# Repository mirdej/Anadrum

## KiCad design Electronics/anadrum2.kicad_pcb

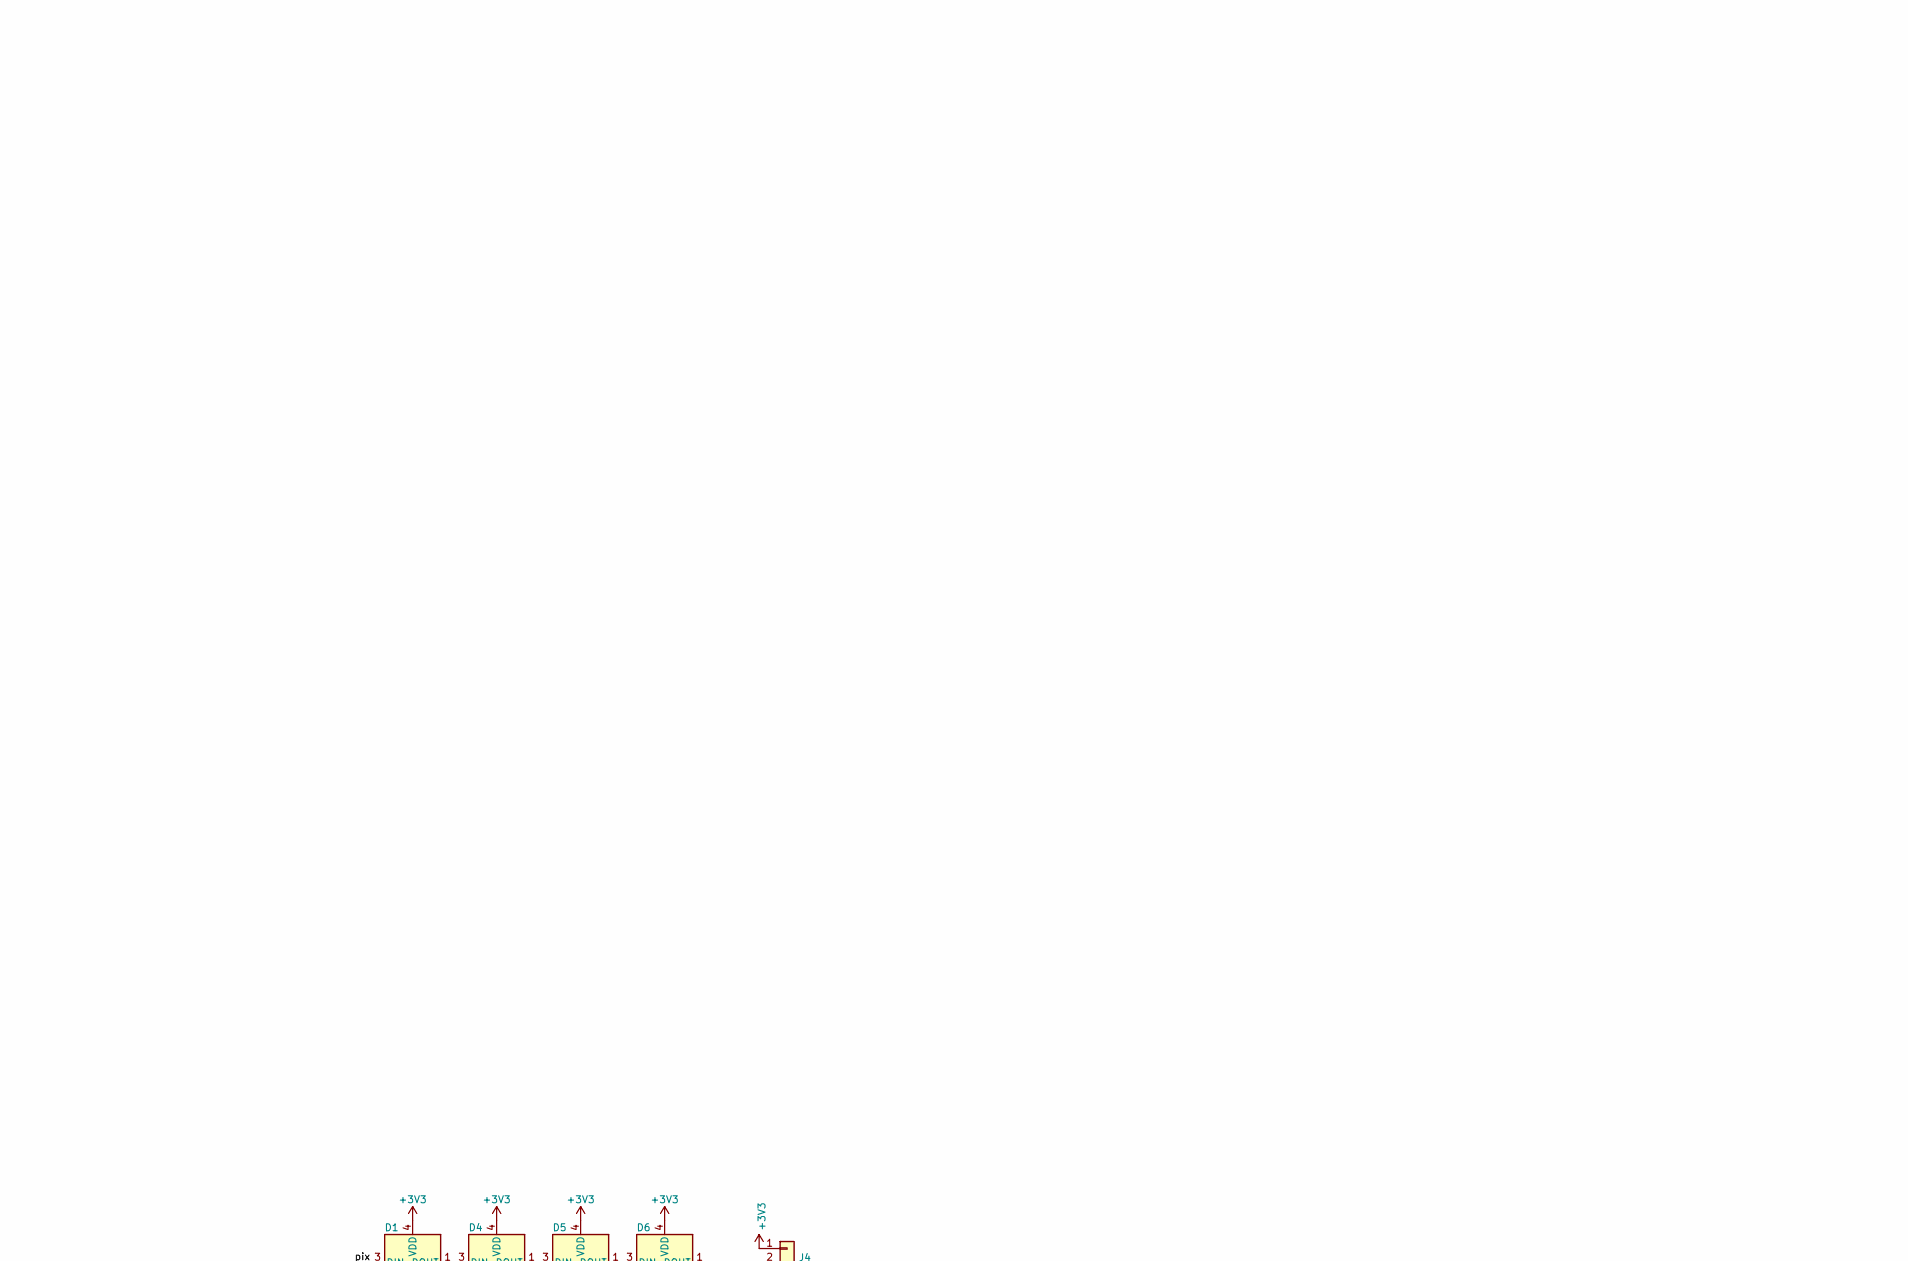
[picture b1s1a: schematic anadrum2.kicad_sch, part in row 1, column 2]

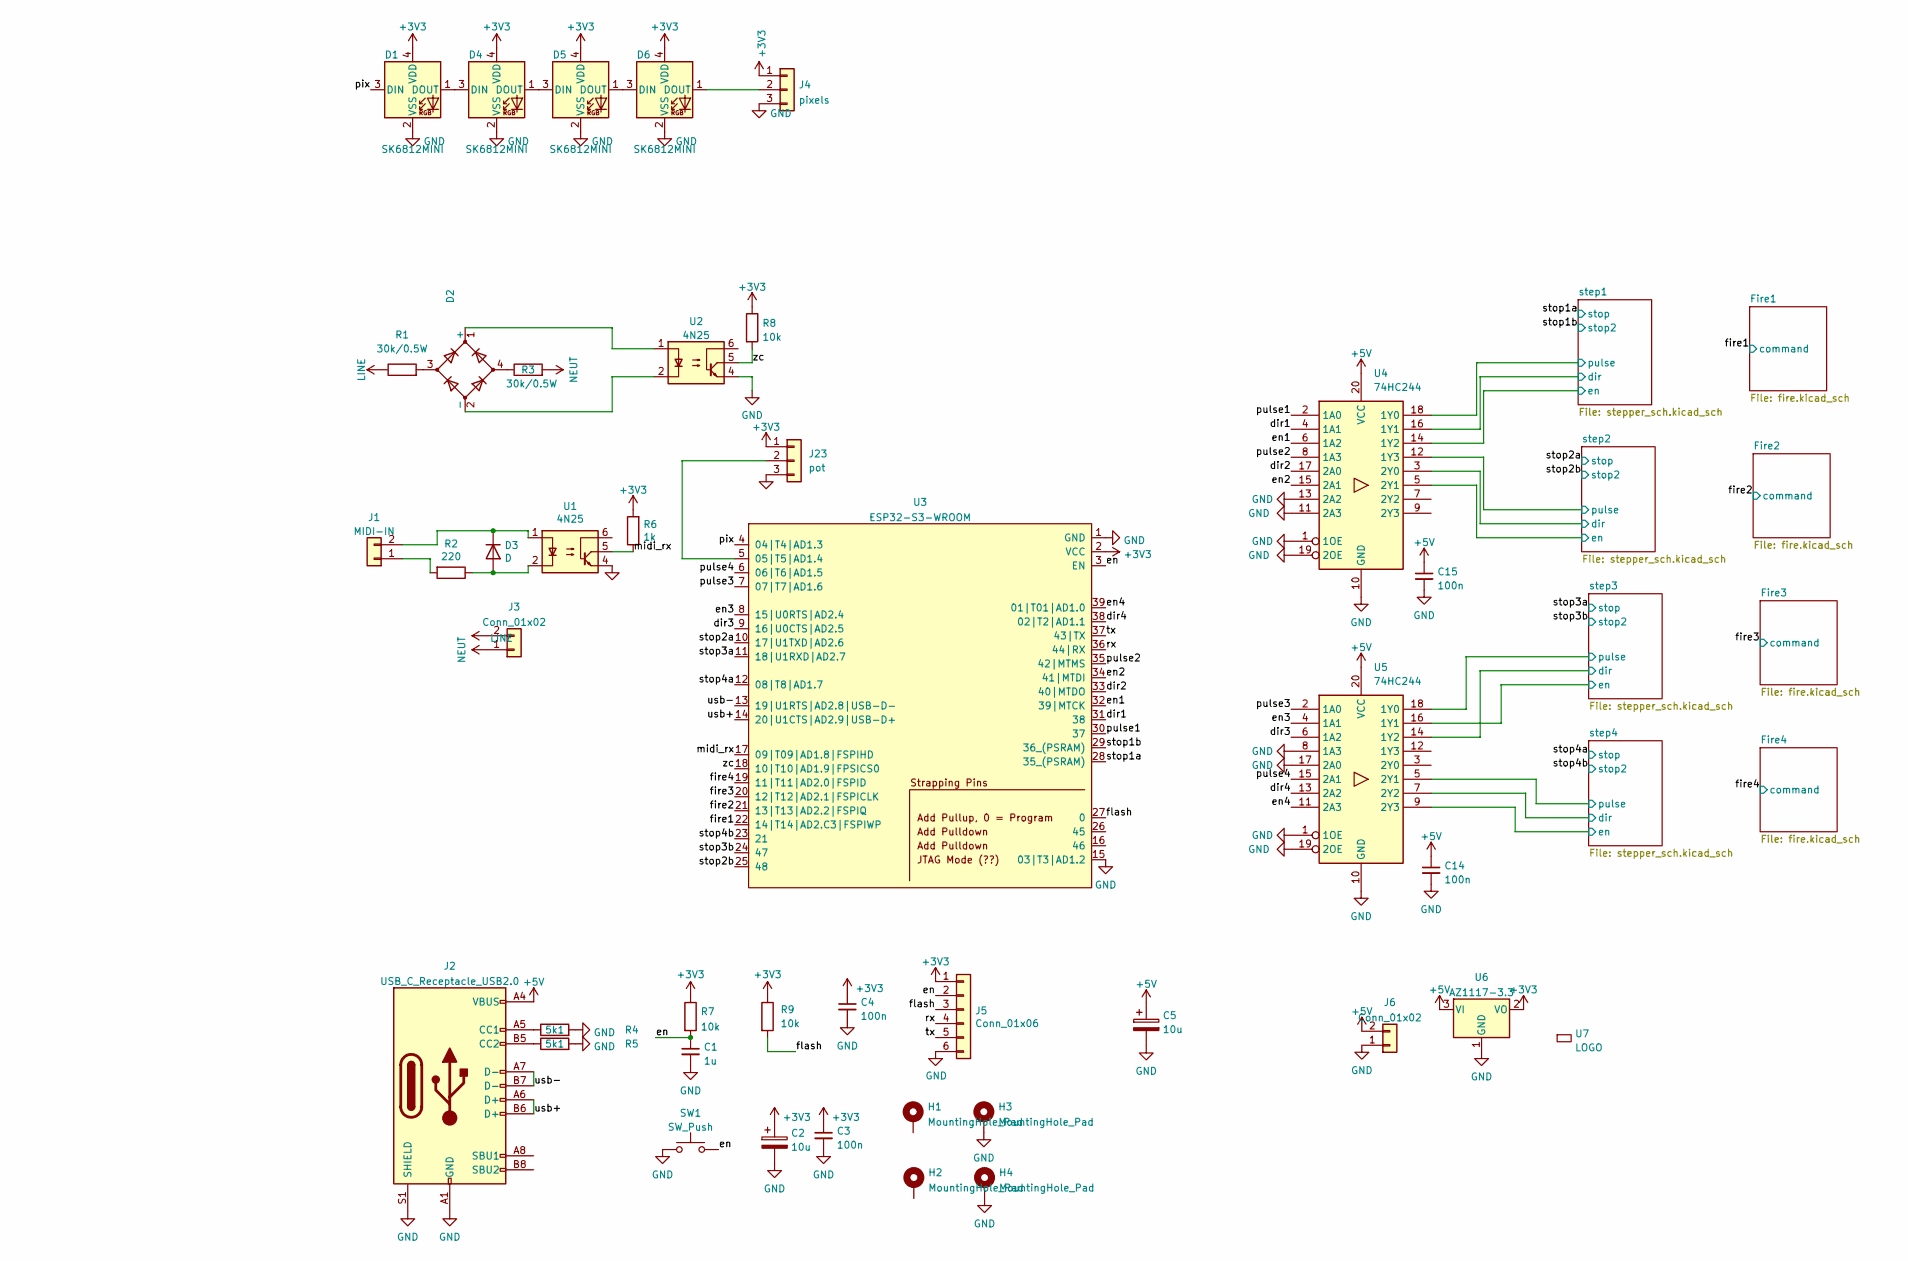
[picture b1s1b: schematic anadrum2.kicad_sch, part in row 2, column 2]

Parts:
C1: 1u; C_0603_1608Metric_Pad1.05x0.95mm_HandSolder
C2, C5: 10u; C_1206_3216Metric_Pad1.42x1.75mm_HandSolder
C3, C4, C14, C15: 100n; C_0603_1608Metric_Pad1.05x0.95mm_HandSolder
D1, D4, D5, D6: SK6812MINI; LED_SK6812MINI_PLCC4_3.5x3.5mm_P1.75mm
D2: D_Bridge_+-AA; Diode_Bridge_Vishay_DFS
D3: D; D_MiniMELF
H1, H2, H3, H4: MountingHole_Pad; MountingHole_2.5mm_Pad
J1: MIDI-IN; Molex_KK-254_AE-6410-02A_1x02_P2.54mm_Vertical
J2: USB_C_Receptacle_USB2.0; JAE_USB-C_SJ122205
J3, J6: Conn_01x02; Molex_Mini-Fit_Jr_5566-02A_2x01_P4.20mm_Vertical
J4: pixels; ComboPinhead_03
J5: Conn_01x06; AnymaPOGO-ESP
J23: pot; PinHeader_1x03_P2.54mm_Vertical
R1, R3: 30k/0.5W; R_0805_2012Metric
R2: 220; R_0805_2012Metric_Pad1.15x1.40mm_HandSolder
R4, R5: 5k1; R_0805_2012Metric_Pad1.15x1.40mm_HandSolder
R6: 1k; R_0805_2012Metric_Pad1.15x1.40mm_HandSolder
R7, R9: 10k; R_0805_2012Metric_Pad1.15x1.40mm_HandSolder
R8: 10k; R_0805_2012Metric
SW1: SW_Push; MiniButtonPLCC4
U1, U2: 4N25; DIP-6_W8.89mm_SMDSocket_LongPads
U3: ESP32-S3-WROOM
U4, U5: 74HC244; SO-20_12.8x7.5mm_P1.27mm
U6: AZ1117-3.3; SOT-223-3_TabPin2
U7: LOGO; logo_anyma

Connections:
+5V: C5.1, C14.1, C15.1, J2.A4 (VBUS), J2.A9 (VBUS), J2.B4 (VBUS), J2.B9 (VBUS), J6.2, U4.20 (VCC), U5.20 (VCC), U6.3 (VI)
/dir1: U3.31 (38), U4.4 (1A1)
/dir2: U3.33 (40|MTDO), U4.17 (2A0)
/dir3: U3.9 (16|U0CTS|AD2.5), U5.6 (1A2)
/dir4: U3.38 (02|T2|AD1.1), U5.13 (2A2)
/en: C1.1, J5.2, R7.2, SW1.2, U3.3 (EN)
/en1: U3.32 (39|MTCK), U4.6 (1A2)
/en2: U3.34 (41|MTDI), U4.15 (2A1)
/en3: U3.8 (15|U0RTS|AD2.4), U5.4 (1A1)
/en4: U3.39 (01|T01|AD1.0), U5.11 (2A3)
/fire1: U3.22 (14|T14|AD2.C3|FSPIWP); also elsewhere on the board
/fire2: U3.21 (13|T13|AD2.2|FSPIQ); also elsewhere on the board
/fire3: U3.20 (12|T12|AD2.1|FSPICLK); also elsewhere on the board
/fire4: U3.19 (11|T11|AD2.0|FSPID); also elsewhere on the board
/flash: J5.3, R9.2, U3.27 (0)
/midi_rx: R6.1, U1.5, U3.17 (09|T09|AD1.8|FSPIHD)
/pix: D1.3 (DIN), U3.4 (04|T4|AD1.3)
/pulse1: U3.30 (37), U4.2 (1A0)
/pulse2: U3.35 (42|MTMS), U4.8 (1A3)
/pulse3: U3.7 (07|T7|AD1.6), U5.2 (1A0)
/pulse4: U3.6 (06|T6|AD1.5), U5.15 (2A1)
/rx: J5.4, U3.36 (44|RX)
/step1/dir: U4.16 (1Y1); also elsewhere on the board
/step1/en: U4.14 (1Y2); also elsewhere on the board
/step1/pulse: U4.18 (1Y0); also elsewhere on the board
/step2/dir: U4.3 (2Y0); also elsewhere on the board
/step2/en: U4.5 (2Y1); also elsewhere on the board
/step2/pulse: U4.12 (1Y3); also elsewhere on the board
/step3/dir: U5.14 (1Y2); also elsewhere on the board
/step3/en: U5.16 (1Y1); also elsewhere on the board
/step3/pulse: U5.18 (1Y0); also elsewhere on the board
/step4/dir: U5.7 (2Y2); also elsewhere on the board
/step4/en: U5.9 (2Y3); also elsewhere on the board
/step4/pulse: U5.5 (2Y1); also elsewhere on the board
/stop1a: U3.28 (35_(PSRAM)); also elsewhere on the board
/stop1b: U3.29 (36_(PSRAM)); also elsewhere on the board
/stop2a: U3.10 (17|U1TXD|AD2.6); also elsewhere on the board
/stop2b: U3.25 (48); also elsewhere on the board
/stop3a: U3.11 (18|U1RXD|AD2.7); also elsewhere on the board
/stop3b: U3.24 (47); also elsewhere on the board
/stop4a: U3.12 (08|T8|AD1.7); also elsewhere on the board
/stop4b: U3.23 (21); also elsewhere on the board
/tx: J5.5, U3.37 (43|TX)
/usb+: J2.A6 (D+), J2.B6 (D+), U3.14 (20|U1CTS|AD2.9|USB-D+)
/usb-: J2.A7 (D-), J2.B7 (D-), U3.13 (19|U1RTS|AD2.8|USB-D-)
/zc: R8.2, U2.5, U3.18 (10|T10|AD1.9|FPSICS0)
GND: C1.2, C2.2, C3.2, C4.2, C5.2, C14.2, C15.2, D1.2 (VSS), D4.2 (VSS), D5.2 (VSS), D6.2 (VSS), H3.1, H4.1, J2.A1 (GND), J2.A12 (GND), J2.B1 (GND), J2.B12 (GND), J2.S1 (SHIELD), J4.3, J5.6, J6.1, J23.3, R4.2, R5.2, SW1.1, U1.4, U2.4, U3.1 (GND), U3.15 (03|T3|AD1.2), U3.40 (GND), U3.41 (GND), U4.1 (1OE), U4.10 (GND), U4.11 (2A3), U4.13 (2A2), U4.19 (2OE), U5.1 (1OE), U5.8 (1A3), U5.10 (GND), U5.17 (2A0), U5.19 (2OE), U6.1 (GND); also elsewhere on the board
LINE: J3.2, R1.1; also elsewhere on the board
NEUT: J3.1, R3.2; also elsewhere on the board
unnamed: D1.1 (DOUT), D4.3 (DIN)
unnamed: D2.1 (+), U2.1
unnamed: D2.2 (-), U2.2
unnamed: D2.3, R1.2
unnamed: D2.4, R3.1
unnamed: D3.2 (A), R2.1, U1.2
unnamed: D3.1 (K), J1.2, U1.1
unnamed: D4.1 (DOUT), D5.3 (DIN)
unnamed: D5.1 (DOUT), D6.3 (DIN)
unnamed: D6.1 (DOUT), J4.2
unnamed: J1.1, R2.2
unnamed: J2.A5 (CC1), R4.1
unnamed: J2.B5 (CC2), R5.1
unnamed: J23.2, U3.5 (05|T5|AD1.4)

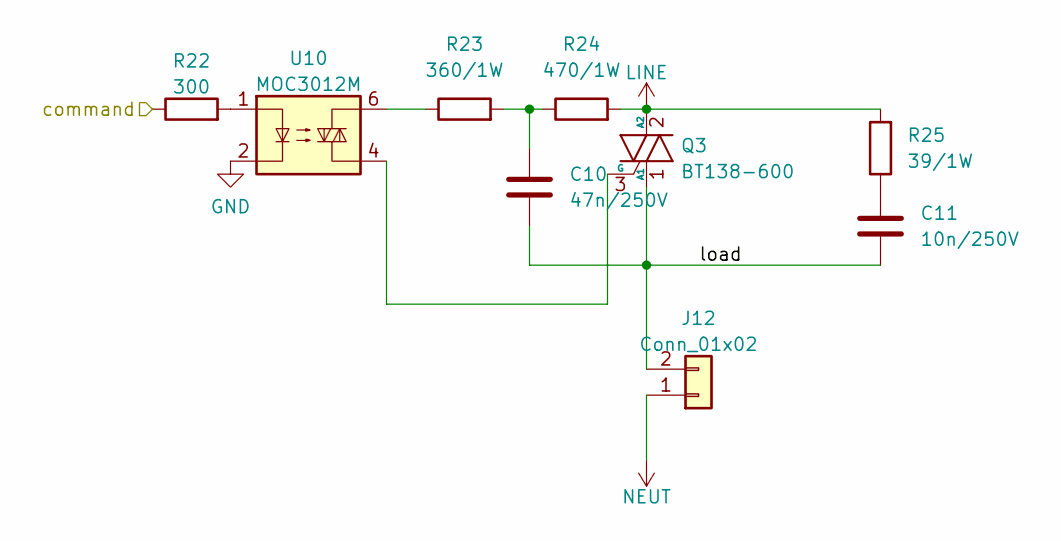
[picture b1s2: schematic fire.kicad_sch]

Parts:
C10: 47n/250V; C_1206_3216Metric_Pad1.42x1.75mm_HandSolder
C11: 10n/250V; C_0805_2012Metric_Pad1.15x1.40mm_HandSolder
J12: Conn_01x02; Molex_Mini-Fit_Jr_5566-02A_2x01_P4.20mm_Vertical
Q3: BT138-600; TO-220-3_Horizontal_TabDown
R22: 300; R_0805_2012Metric
R23: 360/1W; R_2512_6332Metric
R24: 470/1W; R_2512_6332Metric
R25: 39/1W; R_2512_6332Metric
U10: MOC3012M; DIP-6_W8.89mm_SMDSocket_LongPads

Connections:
/Fire1/load: C10.2, C11.2, J12.2, Q3.1 (A1)
/fire1: R22.1; also elsewhere on the board
GND: U10.2; also elsewhere on the board
LINE: Q3.2 (A2), R24.2, R25.2; also elsewhere on the board
NEUT: J12.1; also elsewhere on the board
unnamed: C10.1, R23.2, R24.1
unnamed: C11.1, R25.1
unnamed: Q3.3 (G), U10.4
unnamed: R22.2, U10.1
unnamed: R23.1, U10.6

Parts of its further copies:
C6, C8, C12: 47n/250V; C_1206_3216Metric_Pad1.42x1.75mm_HandSolder
C7, C9, C13: 10n/250V; C_0805_2012Metric_Pad1.15x1.40mm_HandSolder
J7, J11, J19: Conn_01x02; Molex_Mini-Fit_Jr_5566-02A_2x01_P4.20mm_Vertical
Q1, Q2, Q4: BT138-600; TO-220-3_Horizontal_TabDown
R10, R18, R34: 300; R_0805_2012Metric
R11, R19, R35: 360/1W; R_2512_6332Metric
R12, R20, R36: 470/1W; R_2512_6332Metric
R13, R21, R37: 39/1W; R_2512_6332Metric
U8, U9, U11: MOC3012M; DIP-6_W8.89mm_SMDSocket_LongPads

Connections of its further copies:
/Fire2/load: C6.2, C7.2, J7.2, Q1.1 (A1)
/Fire3/load: C8.2, C9.2, J11.2, Q2.1 (A1)
/Fire4/load: C12.2, C13.2, J19.2, Q4.1 (A1)
/fire2: R10.1; also elsewhere on the board
/fire3: R18.1; also elsewhere on the board
/fire4: R34.1; also elsewhere on the board
GND: U8.2, U9.2, U11.2; also elsewhere on the board
LINE: Q1.2 (A2), Q2.2 (A2), Q4.2 (A2), R12.2, R13.2, R20.2, R21.2, R36.2, R37.2; also elsewhere on the board
NEUT: J7.1, J11.1, J19.1; also elsewhere on the board
unnamed: C6.1, R11.2, R12.1
unnamed: C7.1, R13.1
unnamed: C8.1, R19.2, R20.1
unnamed: C9.1, R21.1
unnamed: C12.1, R35.2, R36.1
unnamed: C13.1, R37.1
unnamed: Q1.3 (G), U8.4
unnamed: Q2.3 (G), U9.4
unnamed: Q4.3 (G), U11.4
unnamed: R10.2, U8.1
unnamed: R11.1, U8.6
unnamed: R18.2, U9.1
unnamed: R19.1, U9.6
unnamed: R34.2, U11.1
unnamed: R35.1, U11.6

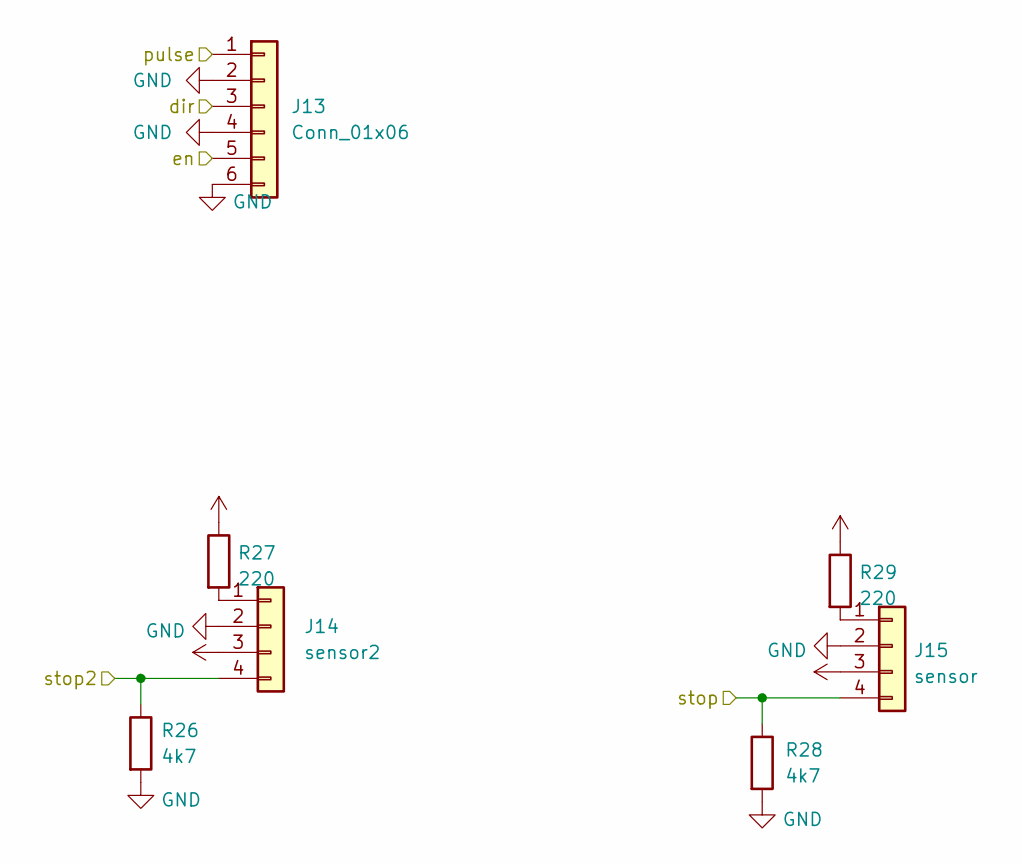
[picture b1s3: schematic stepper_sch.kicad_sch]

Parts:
J13: Conn_01x06; IDC-Header_2x03_P2.54mm_Vertical
J14: sensor2; Molex_KK-254_AE-6410-04A_1x04_P2.54mm_Vertical
J15: sensor; Molex_KK-254_AE-6410-04A_1x04_P2.54mm_Vertical
R26, R28: 4k7; R_0805_2012Metric
R27, R29: 220; R_0805_2012Metric

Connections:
/step1/dir: J13.3; also elsewhere on the board
/step1/en: J13.5; also elsewhere on the board
/step1/pulse: J13.1; also elsewhere on the board
/stop1a: J15.4, R28.1; also elsewhere on the board
/stop1b: J14.4, R26.1; also elsewhere on the board
GND: J13.2, J13.4, J13.6, J14.2, J15.2, R26.2, R28.2; also elsewhere on the board
unnamed: J14.1, R27.2
unnamed: J15.1, R29.2

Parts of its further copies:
J8, J16, J20: Conn_01x06; IDC-Header_2x03_P2.54mm_Vertical
J9, J17, J21: sensor2; Molex_KK-254_AE-6410-04A_1x04_P2.54mm_Vertical
J10, J18, J22: sensor; Molex_KK-254_AE-6410-04A_1x04_P2.54mm_Vertical
R14, R16, R30, R32, R38, R40: 4k7; R_0805_2012Metric
R15, R17, R31, R33, R39, R41: 220; R_0805_2012Metric

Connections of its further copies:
/step2/dir: J8.3; also elsewhere on the board
/step2/en: J8.5; also elsewhere on the board
/step2/pulse: J8.1; also elsewhere on the board
/step3/dir: J16.3; also elsewhere on the board
/step3/en: J16.5; also elsewhere on the board
/step3/pulse: J16.1; also elsewhere on the board
/step4/dir: J20.3; also elsewhere on the board
/step4/en: J20.5; also elsewhere on the board
/step4/pulse: J20.1; also elsewhere on the board
/stop2a: J10.4, R16.1; also elsewhere on the board
/stop2b: J9.4, R14.1; also elsewhere on the board
/stop3a: J18.4, R32.1; also elsewhere on the board
/stop3b: J17.4, R30.1; also elsewhere on the board
/stop4a: J22.4, R40.1; also elsewhere on the board
/stop4b: J21.4, R38.1; also elsewhere on the board
GND: J8.2, J8.4, J8.6, J9.2, J10.2, J16.2, J16.4, J16.6, J17.2, J18.2, J20.2, J20.4, J20.6, J21.2, J22.2, R14.2, R16.2, R30.2, R32.2, R38.2, R40.2; also elsewhere on the board
unnamed: J9.1, R15.2
unnamed: J10.1, R17.2
unnamed: J17.1, R31.2
unnamed: J18.1, R33.2
unnamed: J21.1, R39.2
unnamed: J22.1, R41.2

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
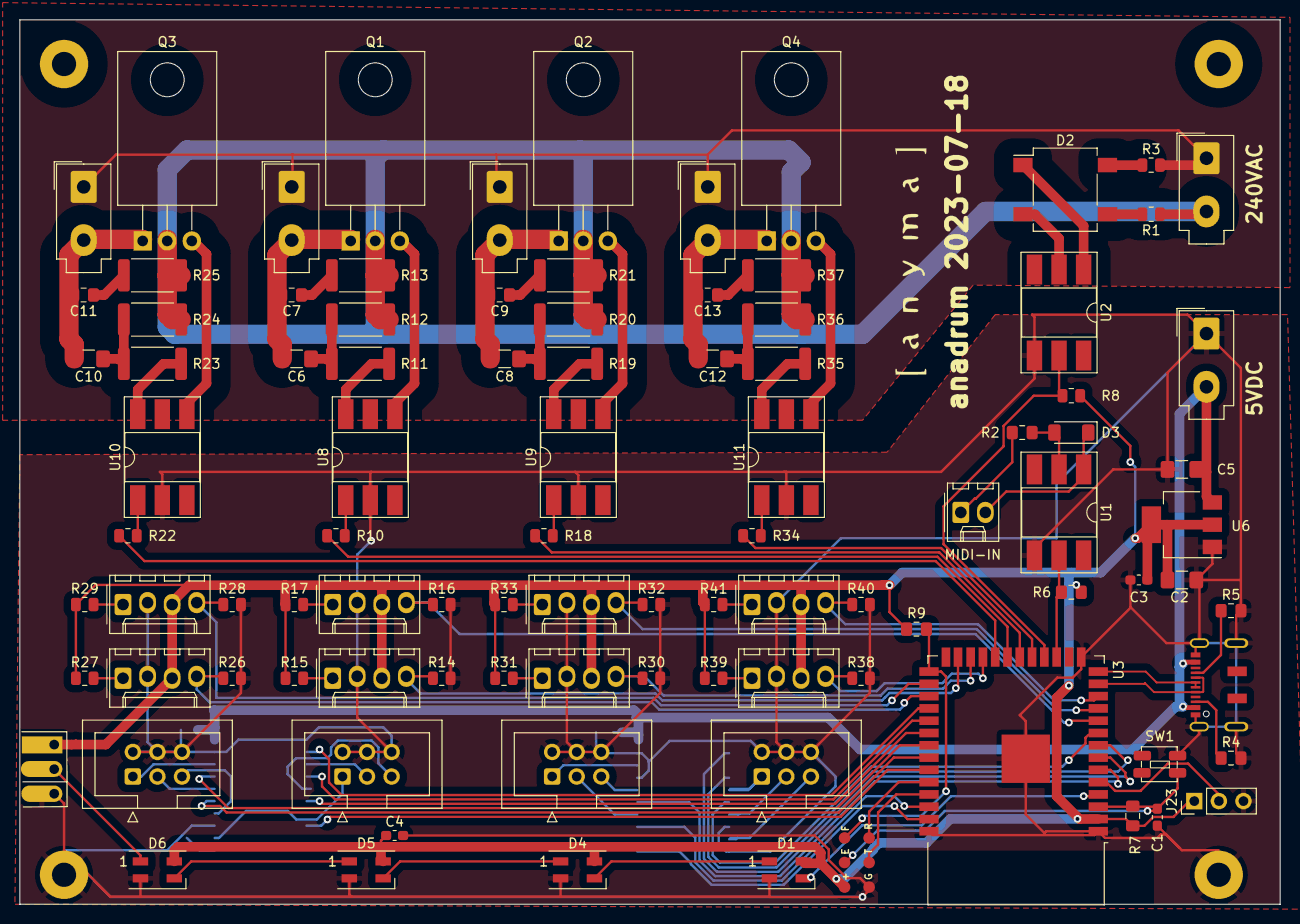
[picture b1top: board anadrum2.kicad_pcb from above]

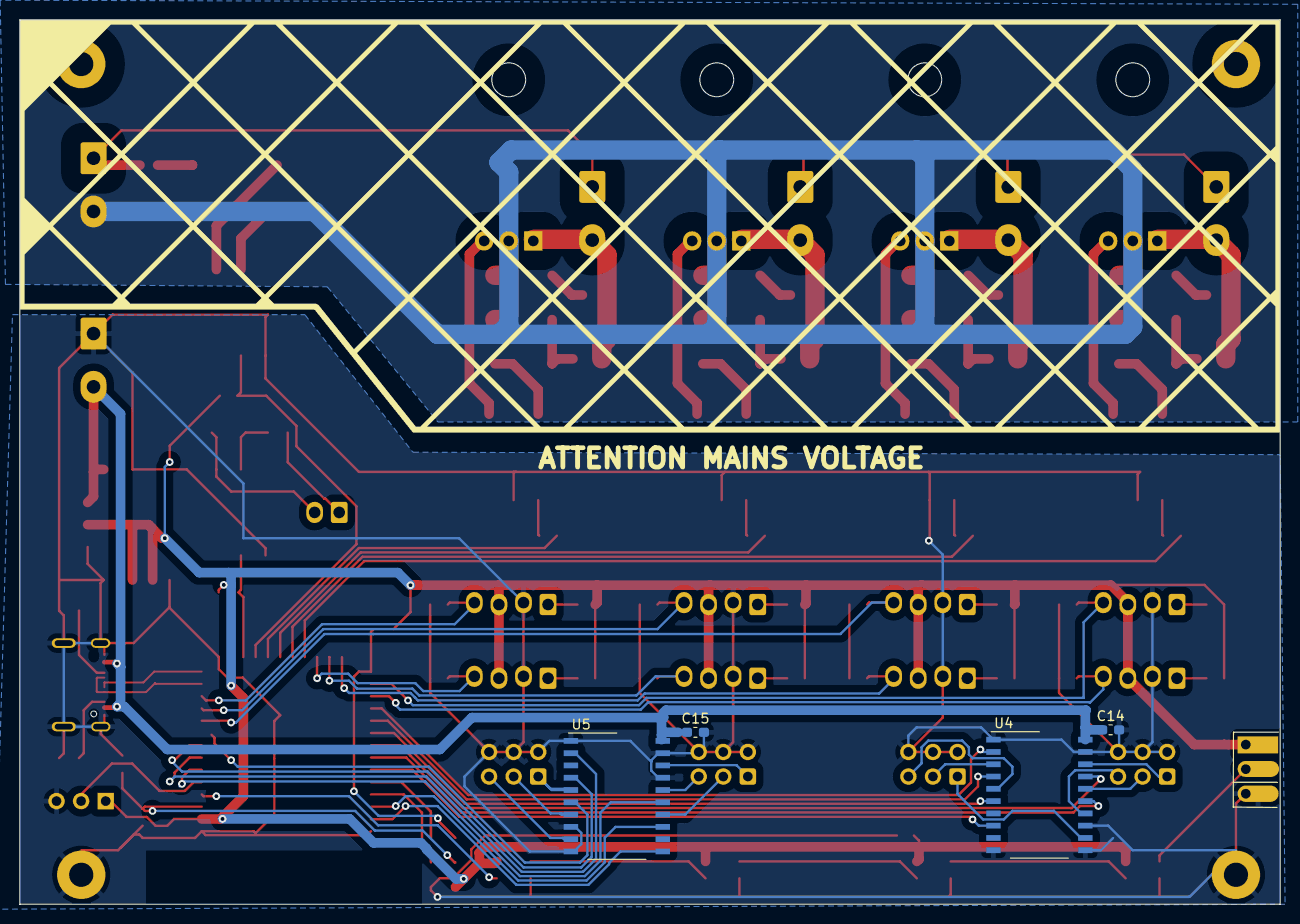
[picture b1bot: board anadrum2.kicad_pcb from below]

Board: 2 copper layers, 130.3 x 91.4 mm, 105 parts (4 on the bottom side), 96 nets.

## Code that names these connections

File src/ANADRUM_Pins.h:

#pragma once

const int PIN_PIX = 4;
const int PIN_POT = 5;
const int PIN_PULSE[] = {37, 42, 7, 6};
const int PIN_ENABLE[] = {39, 41, 15, 1};
const int PIN_DIR[] = {38, 40, 16, 2};
const int PIN_STOP_A[] ={35,17,18,8};
const int PIN_MIDI_RX = 9;
const int PIN_ZEROCROSS = 10;
const int PIN_FIRE[] = {14,13,12,11};
const int PIN_STOP_B[] ={36,48,47,21};

const int PIN_LEARN = 47;
const int PIN_MIDI_TX = 36;

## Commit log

2023-08-22 initial commit. Pix work
2023-08-24 more efficient motor loop
2023-08-24 add midi force-control
2023-10-19 change direction for new hardware
2023-10-19 learn notes
2024-05-09 fixes for first realworld test
2024-05-09 move firmware to subfolder
2024-05-09 Add harware
